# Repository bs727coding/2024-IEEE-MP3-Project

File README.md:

# 2024-IEEE-MP3-Project

A simple media player with bluetooth support using an ESP32, LCD display, audio driver, battery, and button controls.

This is a part of the Brigham Young University IEEE student branch 2024-2025 project.

There are 4 outcomes we hope to accomplish with this project. These are:

    Develop an understanding of KiCAD and PCB design, including footprint design, schematic development, and design rules.
    Learn embedded programming by using FreeRTOS and C to program an ESP32 microcontroller to process media files and control its input and output functions.
    Acquire skill in how to use CAD softwares to design an appropriate chassis for electrical components.
    Become confident and consistent in electrical engineering project documentation.

We anticipate this project will be exciting, challenging, and provide participating students an opportunity to grow their engineering skills outside of a classroom setting.

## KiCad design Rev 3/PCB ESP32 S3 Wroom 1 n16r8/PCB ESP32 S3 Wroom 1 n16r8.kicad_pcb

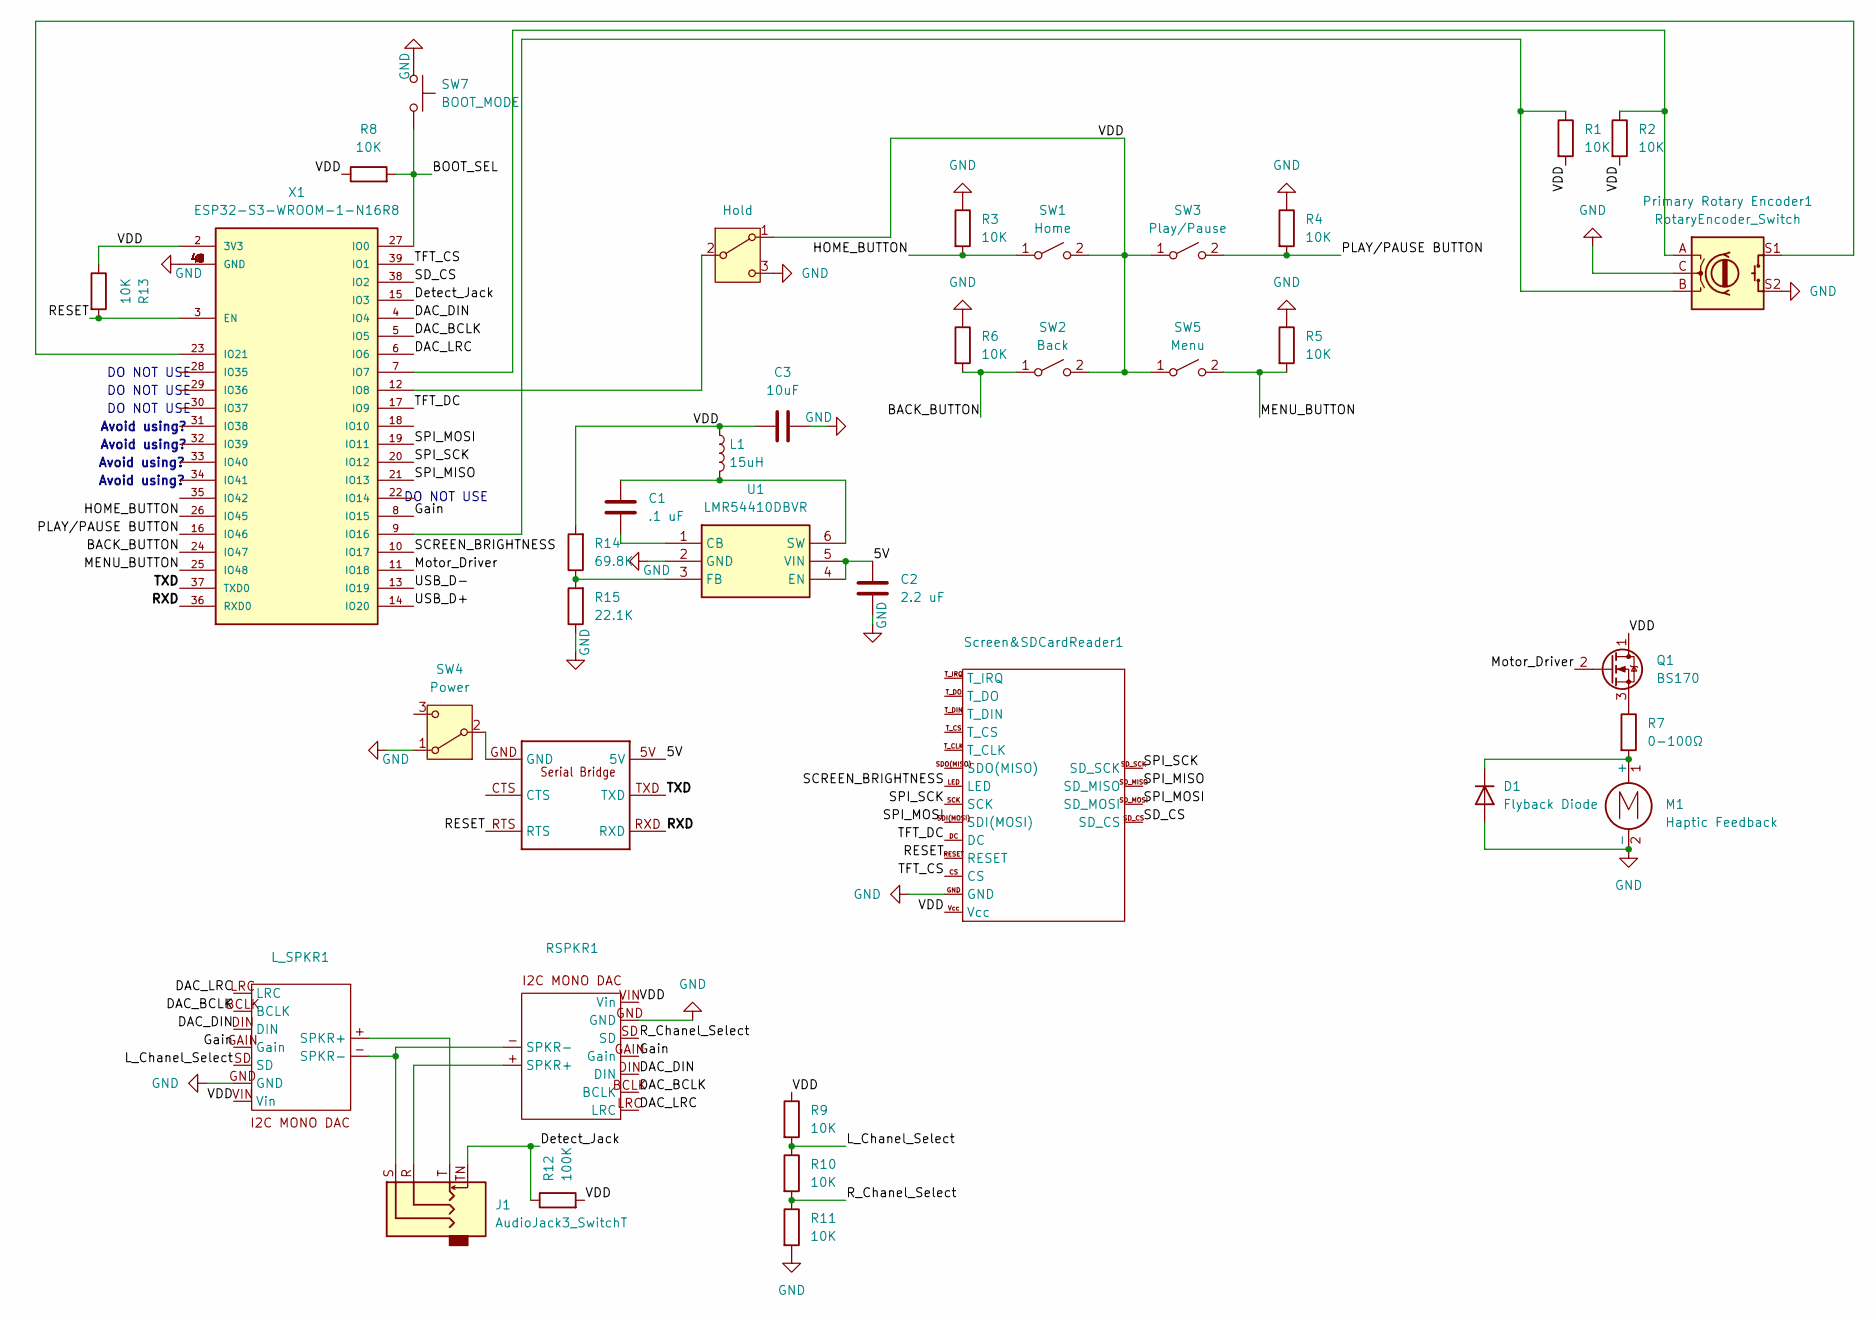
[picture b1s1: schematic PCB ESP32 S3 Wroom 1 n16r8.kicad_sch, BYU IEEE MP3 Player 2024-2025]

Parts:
1: UART_FTDI
C1: .1 uF; C_0603_1608Metric
C2: 2.2 uF; C_0603_1608Metric
C3: 10uF; C_0603_1608Metric
D1: Flyback Diode; D_A-405_P7.62mm_Horizontal
J1: AudioJack3_SwitchT; Jack_3.5mm_CUI_SJ1-3524N_Horizontal
L1: 15uH; L_Vishay_IFSC-1515AH_4x4x1.8mm
L_SPKR1: MAX98357 I2C Audio Driver
M1: Haptic Feedback; TerminalBlock_RND_205-00001_1x02_P5.00mm_Horizontal
Primary Rotary Encoder1: RotaryEncoder_Switch; RotaryEncoder_Alps_EC11E-Switch_Vertical_H20mm
Q1: BS170; TO-92_Inline
R1, R2, R3, R4, R5, R6, R8, R9, R10, R11, R13: 10K; R_Axial_DIN0204_L3.6mm_D1.6mm_P7.62mm_Horizontal
R7: 0-100Ω; R_Axial_DIN0204_L3.6mm_D1.6mm_P7.62mm_Horizontal
R12: 100K; R_Axial_DIN0204_L3.6mm_D1.6mm_P7.62mm_Horizontal
R14: 69.8K; R_01005_0402Metric_Pad0.57x0.30mm_HandSolder
R15: 22.1K; R_01005_0402Metric_Pad0.57x0.30mm_HandSolder
RSPKR1: MAX98357 I2C Audio Driver
SW1: Home; Kailh_socket_PG1350
SW2: Back; Kailh_socket_PG1350
SW3: Play/Pause; Kailh_socket_PG1350
SW4: Power; SW_Slide_SPDT_Angled_CK_OS102011MA1Q
SW5: Menu; Kailh_socket_PG1350
SW6: Hold; SW_Slide_SPDT_Angled_CK_OS102011MA1Q
SW7: BOOT_MODE; SW_PUSH_6mm
Screen&SDCardReader1: 2.4'_TFT_SPI_ILI9341_WITH_SD_CARD
U1: LMR54410DBVR; SOT95P280X145-6N; Mouser Part Number 595-LMR54410DBVR
X1: ESP32-S3-WROOM-1-N16R8; ESP32S3WROOM1N8R2; MANUFACTURER_PART_NUMBER ESP32-S3-WROOM-1-N16R8

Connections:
/5V: 1.5V, C2.2, U1.4 (EN), U1.5 (VIN)
/BACK_BUTTON: R6.2, SW2.1 (A), X1.24 (IO47)
/BOOT_SEL: R8.2, SW7.2, X1.27 (IO0)
/DAC_BCLK: L_SPKR1.BCLK, RSPKR1.BCLK, X1.5 (IO5)
/DAC_DIN: L_SPKR1.DIN, RSPKR1.DIN, X1.4 (IO4)
/DAC_LRC: L_SPKR1.LRC, RSPKR1.LRC, X1.6 (IO6)
/Detect_Jack: J1.TN, R12.1, X1.15 (IO3)
/Gain: L_SPKR1.GAIN (Gain), RSPKR1.GAIN (Gain), X1.8 (IO15)
/HOME_BUTTON: R3.2, SW1.1 (A), X1.26 (IO45)
/L_Chanel_Select: L_SPKR1.SD, R9.2, R10.1
/MENU_BUTTON: R5.2, SW5.2 (B), X1.25 (IO48)
/Motor_Driver: Q1.2 (G), X1.11 (IO18)
/PLAY/PAUSE BUTTON: R4.2, SW3.2 (B), X1.16 (IO46)
/RESET: 1.RTS, R13.2, Screen&SDCardReader1.RESET, X1.3 (EN)
/RXD: 1.RXD, X1.36 (RXD0)
/R_Chanel_Select: R10.2, R11.1, RSPKR1.SD
/SCREEN_BRIGHTNESS: Screen&SDCardReader1.LED, X1.10 (IO17)
/SD_CS: Screen&SDCardReader1.SD_CS, X1.38 (IO2)
/SPI_MISO: Screen&SDCardReader1.SD_MISO, X1.21 (IO13)
/SPI_MOSI: Screen&SDCardReader1.SDI(MOSI), Screen&SDCardReader1.SD_MOSI, X1.19 (IO11)
/SPI_SCK: Screen&SDCardReader1.SCK, Screen&SDCardReader1.SD_SCK, X1.20 (IO12)
/TFT_CS: Screen&SDCardReader1.CS, X1.39 (IO1)
/TFT_DC: Screen&SDCardReader1.DC, X1.17 (IO9)
/TXD: 1.TXD, X1.37 (TXD0)
/USB_D+: X1.14 (IO20)
/USB_D-: X1.13 (IO19)
/VDD: C3.2, L1.1, L_SPKR1.VIN (Vin), Q1.1 (D), R1.2, R2.2, R8.1, R9.1, R12.2, R13.1, R14.2, RSPKR1.VIN (Vin), SW1.2 (B), SW2.2 (B), SW3.1 (A), SW5.1 (A), SW6.1 (A), Screen&SDCardReader1.Vcc, X1.2 (3V3)
GND: C2.1, C3.1, D1.2 (A), L_SPKR1.GND, M1.2 (-), Primary Rotary Encoder1.C, Primary Rotary Encoder1.S2, R3.1, R4.1, R5.1, R6.1, R11.2, R15.1, RSPKR1.GND, SW4.1 (A), SW6.3 (C), SW7.1, Screen&SDCardReader1.GND, U1.2 (GND), X1.1 (GND), X1.40 (GND), X1.41 (GND), X1.42 (GND), X1.43 (GND), X1.44 (GND), X1.45 (GND), X1.46 (GND), X1.47 (GND), X1.48 (GND), X1.49 (GND)
unnamed: D1.1 (K), M1.1 (+), R7.2
unnamed: J1.T, L_SPKR1.+ (SPKR+)
unnamed: J1.S, L_SPKR1.- (SPKR-), RSPKR1.- (SPKR-)
unnamed: Q1.3 (S), R7.1
unnamed: J1.R, RSPKR1.+ (SPKR+)
unnamed: 1.GND, SW4.2 (B)
unnamed: SW6.2 (B), X1.12 (IO8)
unnamed: C1.2, U1.1 (CB)
unnamed: R14.1, R15.2, U1.3 (FB)
unnamed: C1.1, L1.2, U1.6 (SW)
unnamed: Primary Rotary Encoder1.A, R2.1, X1.7 (IO7)
unnamed: Primary Rotary Encoder1.B, R1.1, X1.9 (IO16)
unnamed: Primary Rotary Encoder1.S1, X1.23 (IO21)

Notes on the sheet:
Avoid using?
DO NOT USE

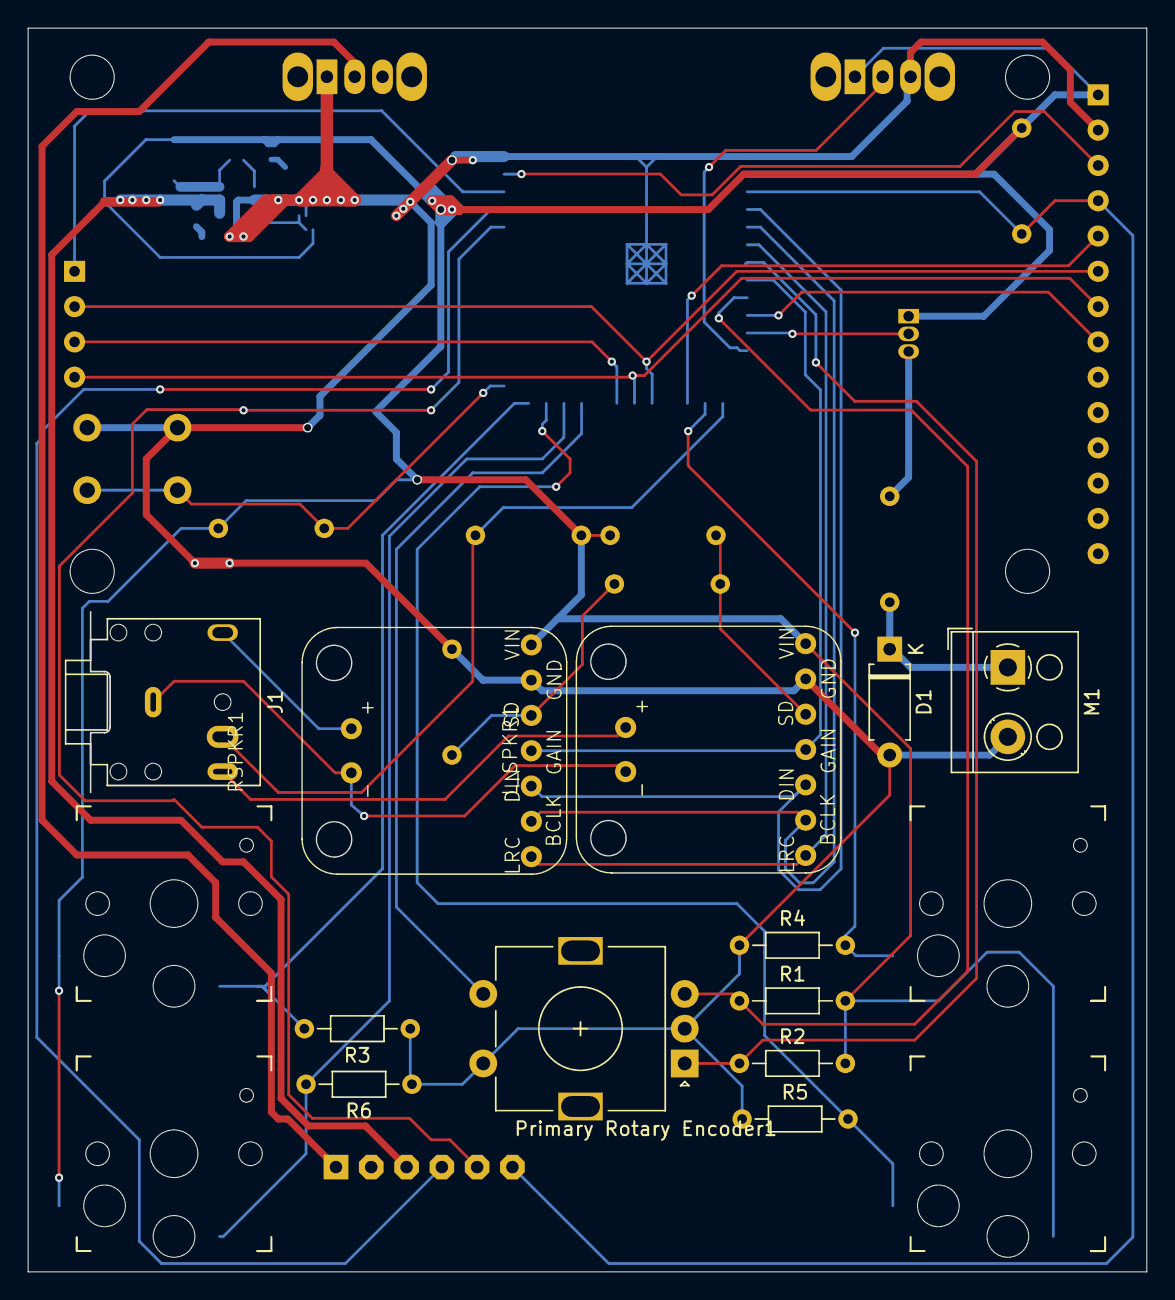
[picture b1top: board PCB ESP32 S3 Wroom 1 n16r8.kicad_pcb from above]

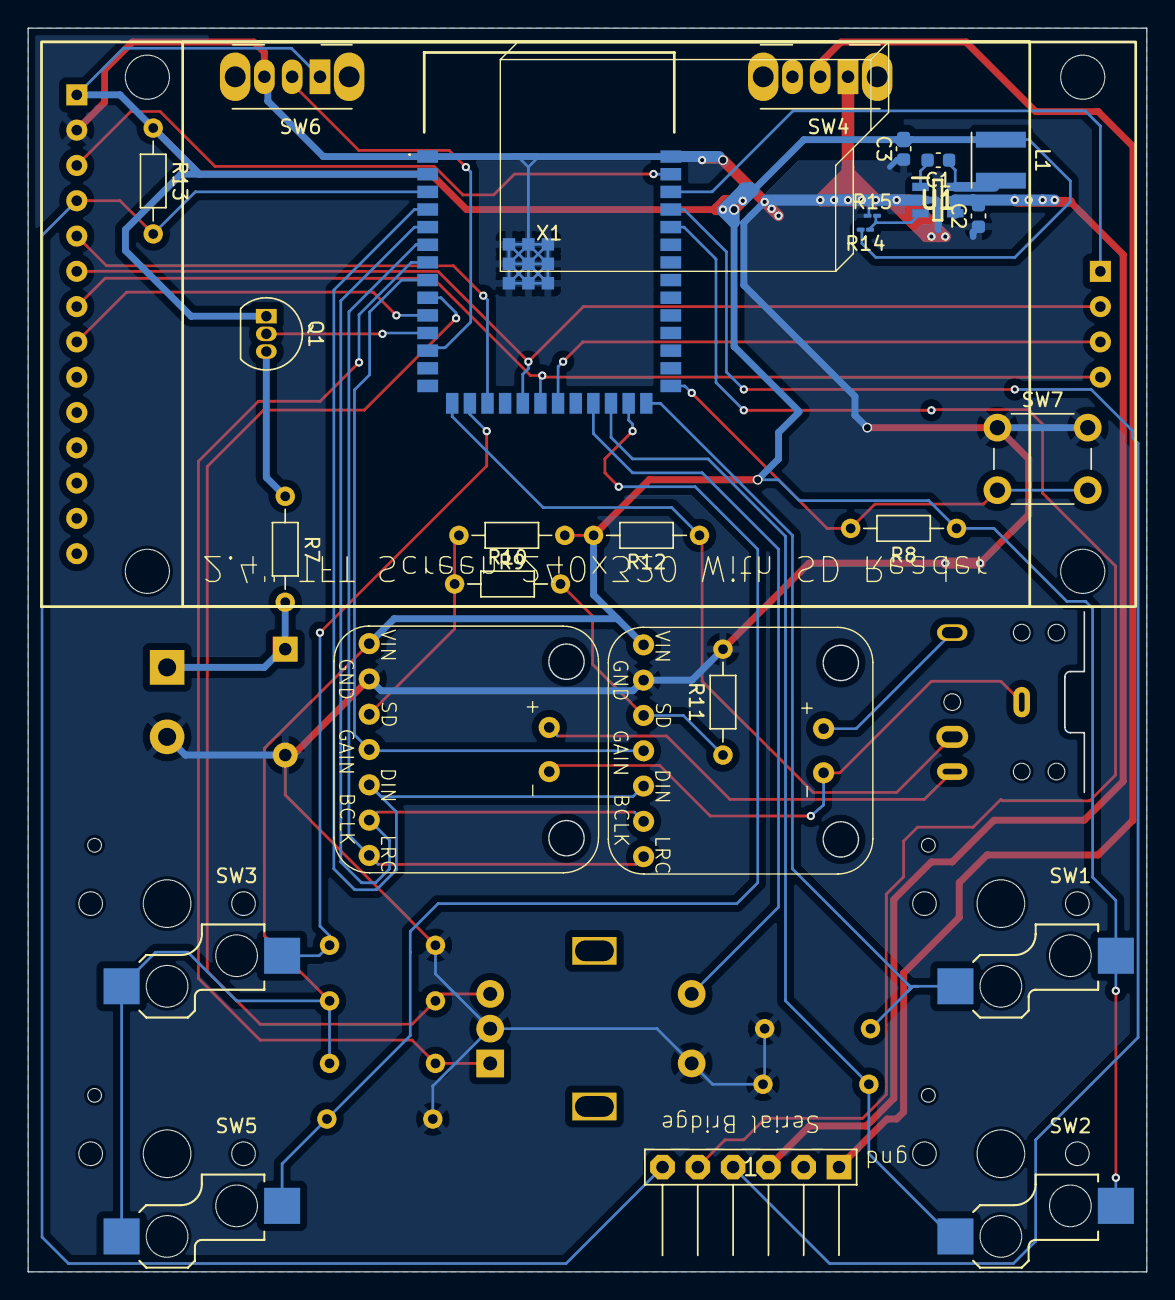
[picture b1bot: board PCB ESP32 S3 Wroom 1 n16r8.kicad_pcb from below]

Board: 2 copper layers, 80.5 x 89.5 mm, 37 parts (20 on the bottom side), 39 nets.

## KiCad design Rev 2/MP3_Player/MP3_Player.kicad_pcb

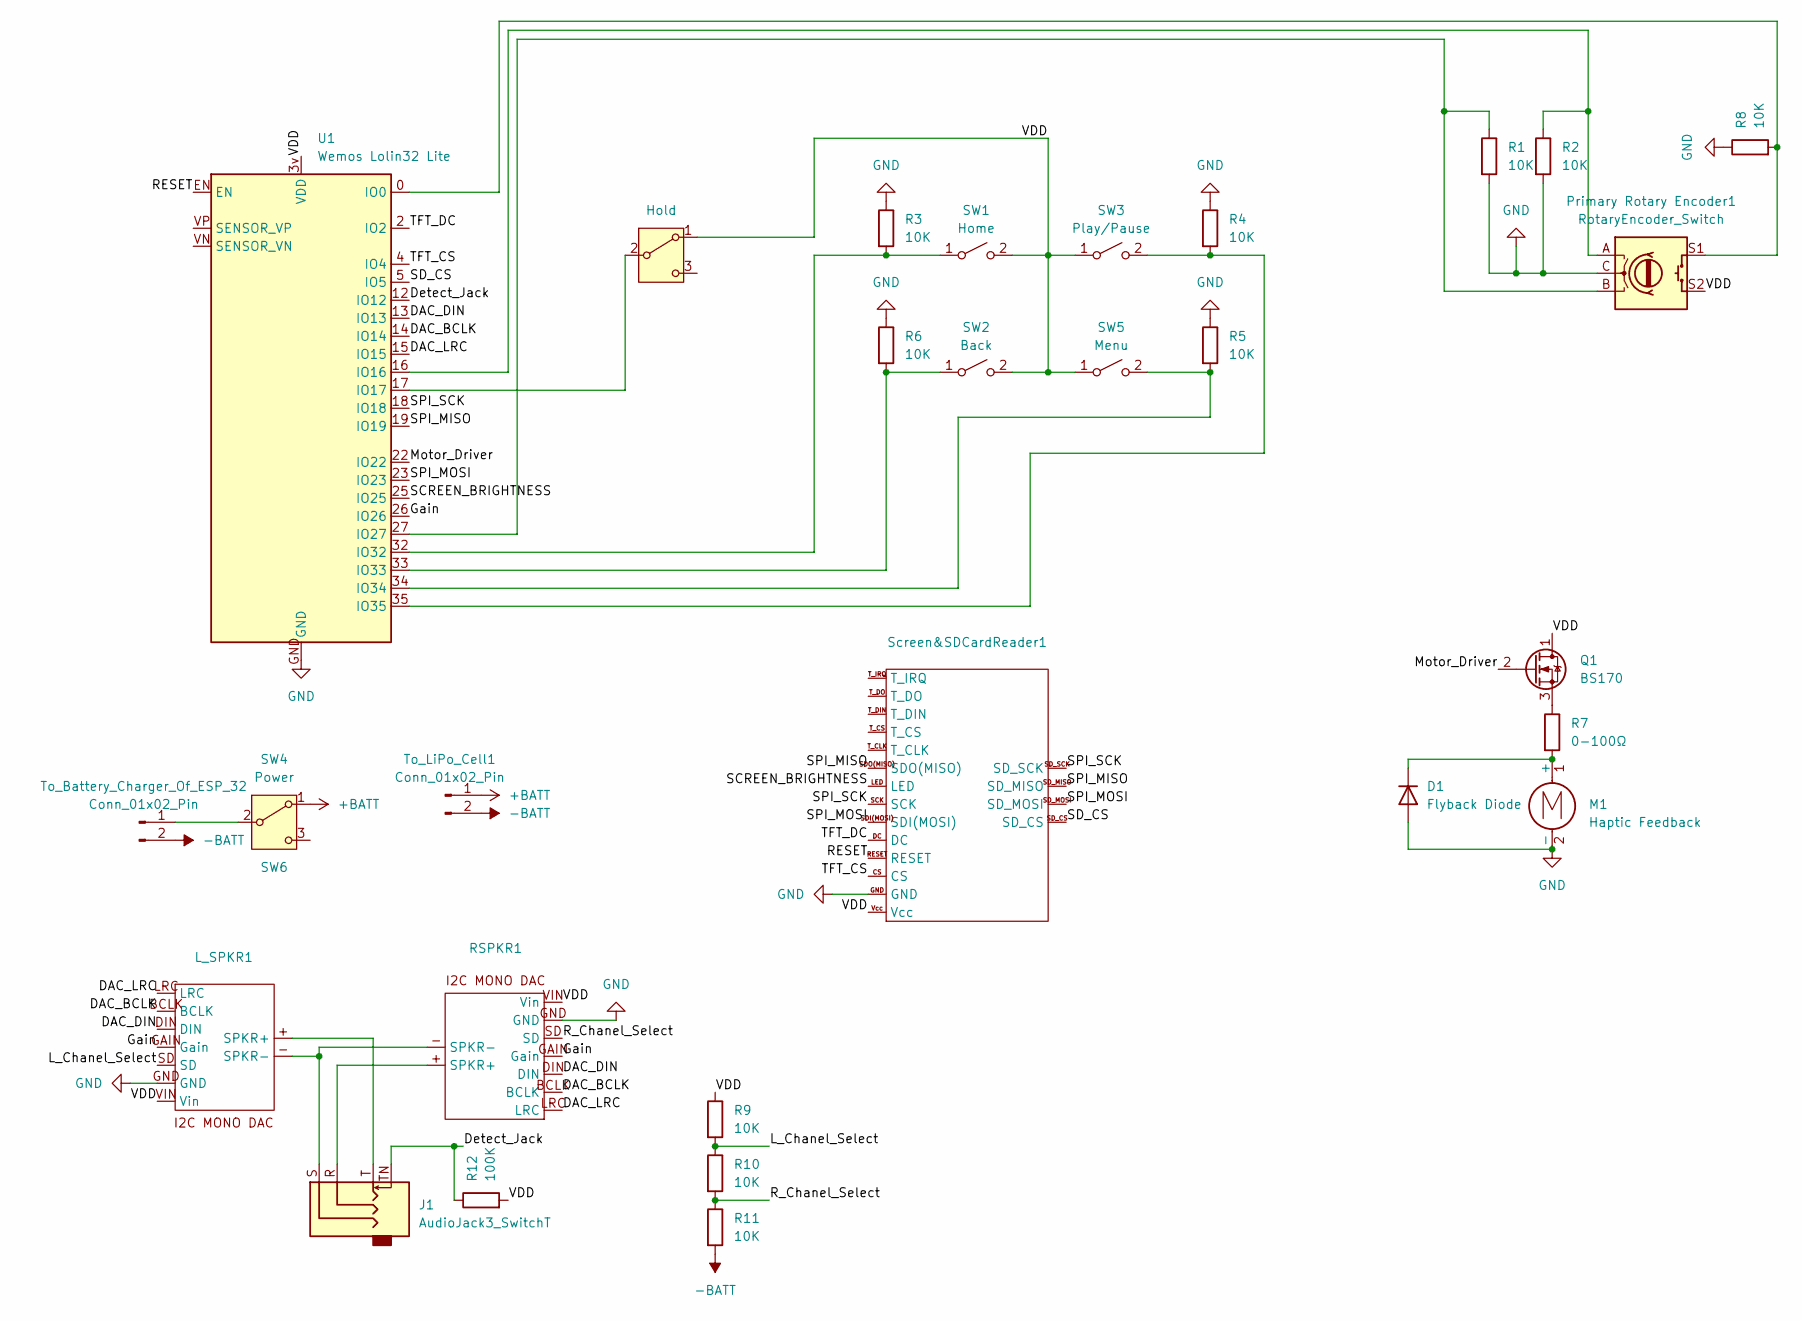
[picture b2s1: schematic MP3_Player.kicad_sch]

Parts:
D1: Flyback Diode; D_A-405_P7.62mm_Horizontal
J1: AudioJack3_SwitchT; Jack_3.5mm_CUI_SJ1-3524N_Horizontal
L_SPKR1: MAX98357 I2C Audio Driver
M1: Haptic Feedback; TerminalBlock_RND_205-00001_1x02_P5.00mm_Horizontal
Primary Rotary Encoder1: RotaryEncoder_Switch; RotaryEncoder_Alps_EC11E-Switch_Vertical_H20mm
Q1: BS170; TO-92_Inline
R1, R2, R3, R4, R5, R6, R8, R9, R10, R11: 10K; R_Axial_DIN0204_L3.6mm_D1.6mm_P7.62mm_Horizontal
R7: 0-100Ω; R_Axial_DIN0204_L3.6mm_D1.6mm_P7.62mm_Horizontal
R12: 100K; R_Axial_DIN0204_L3.6mm_D1.6mm_P7.62mm_Horizontal
RSPKR1: MAX98357 I2C Audio Driver
SW1: Home; Kailh_socket_PG1350
SW2: Back; Kailh_socket_PG1350
SW3: Play/Pause; Kailh_socket_PG1350
SW4: Power; SW_Slide_SPDT_Angled_CK_OS102011MA1Q
SW5: Menu; Kailh_socket_PG1350
SW6: Hold; SW_Slide_SPDT_Angled_CK_OS102011MA1Q
Screen&SDCardReader1: 2.4'_TFT_SPI_ILI9341_WITH_SD_CARD
To_Battery_Charger_Of_ESP_32: Conn_01x02_Pin; JST_XA_B02B-XASK-1-A_1x02_P2.50mm_Vertical
To_LiPo_Cell1: Conn_01x02_Pin; JST_XA_B02B-XASK-1-A_1x02_P2.50mm_Vertical
U1: Wemos Lolin32 Lite; Wemos Lolin32 Lite v1.0.0

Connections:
+BATT: SW4.1 (A), To_LiPo_Cell1.1
-BATT: R11.2, To_Battery_Charger_Of_ESP_32.2, To_LiPo_Cell1.2
/DAC_BCLK: L_SPKR1.BCLK, RSPKR1.BCLK, U1.14 (IO14)
/DAC_DIN: L_SPKR1.DIN, RSPKR1.DIN, U1.13 (IO13)
/DAC_LRC: L_SPKR1.LRC, RSPKR1.LRC, U1.15 (IO15)
/Detect_Jack: J1.TN, R12.1, U1.12 (IO12)
/Gain: L_SPKR1.GAIN (Gain), RSPKR1.GAIN (Gain), U1.26 (IO26)
/L_Chanel_Select: L_SPKR1.SD, R9.2, R10.1
/Motor_Driver: Q1.2 (G), U1.22 (IO22)
/RESET: Screen&SDCardReader1.RESET, U1.EN
/R_Chanel_Select: R10.2, R11.1, RSPKR1.SD
/SCREEN_BRIGHTNESS: Screen&SDCardReader1.LED, U1.25 (IO25)
/SD_CS: Screen&SDCardReader1.SD_CS, U1.5 (IO5)
/SPI_MISO: Screen&SDCardReader1.SDO(MISO), Screen&SDCardReader1.SD_MISO, U1.19 (IO19)
/SPI_MOSI: Screen&SDCardReader1.SDI(MOSI), Screen&SDCardReader1.SD_MOSI, U1.23 (IO23)
/SPI_SCK: Screen&SDCardReader1.SCK, Screen&SDCardReader1.SD_SCK, U1.18 (IO18)
/TFT_CS: Screen&SDCardReader1.CS, U1.4 (IO4)
/TFT_DC: Screen&SDCardReader1.DC, U1.2 (IO2)
/VDD: L_SPKR1.VIN (Vin), Primary Rotary Encoder1.S2, Q1.1 (D), R9.1, R12.2, RSPKR1.VIN (Vin), SW1.2 (B), SW2.2 (B), SW3.1 (A), SW5.1 (A), SW6.1 (A), Screen&SDCardReader1.Vcc, U1.3v (VDD)
GND: D1.2 (A), L_SPKR1.GND, M1.2 (-), Primary Rotary Encoder1.C, R1.2, R2.2, R3.1, R4.1, R5.1, R6.1, R8.1, RSPKR1.GND, Screen&SDCardReader1.GND, U1.GND
unnamed: D1.1 (K), M1.1 (+), R7.2
unnamed: J1.T, L_SPKR1.+ (SPKR+)
unnamed: J1.S, L_SPKR1.- (SPKR-), RSPKR1.- (SPKR-)
unnamed: Q1.3 (S), R7.1
unnamed: J1.R, RSPKR1.+ (SPKR+)
unnamed: R3.2, SW1.1 (A), U1.32 (IO32)
unnamed: R6.2, SW2.1 (A), U1.33 (IO33)
unnamed: R4.2, SW3.2 (B), U1.35 (IO35)
unnamed: SW4.2 (B), To_Battery_Charger_Of_ESP_32.1
unnamed: R5.2, SW5.2 (B), U1.34 (IO34)
unnamed: SW6.2 (B), U1.17 (IO17)
unnamed: Primary Rotary Encoder1.S1, R8.2, U1.0 (IO0)
unnamed: Primary Rotary Encoder1.A, R2.1, U1.16 (IO16)
unnamed: Primary Rotary Encoder1.B, R1.1, U1.27 (IO27)

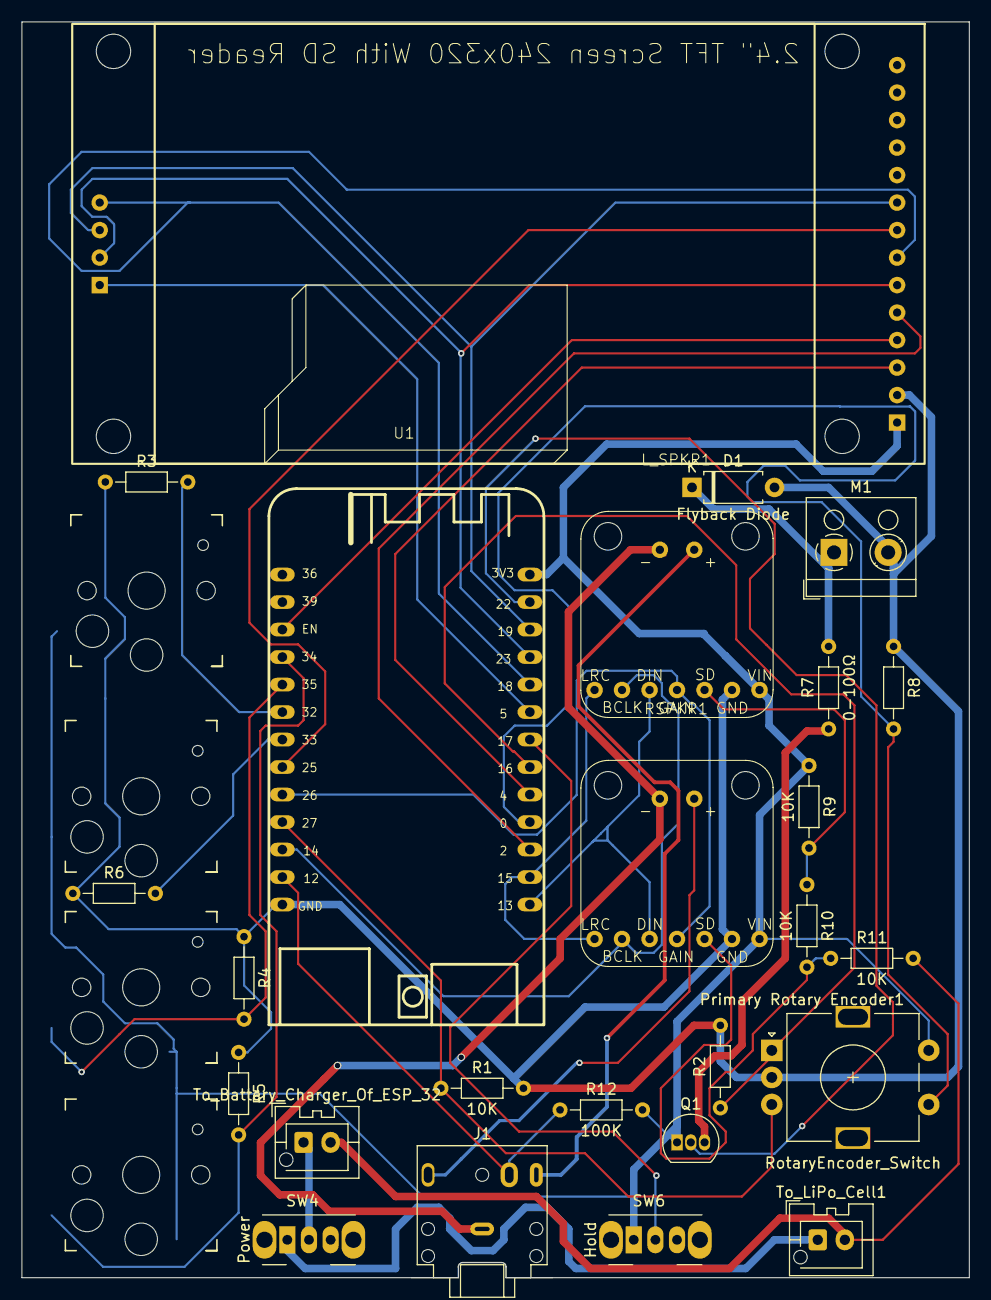
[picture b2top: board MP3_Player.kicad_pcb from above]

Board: 2 copper layers, 87.5 x 116.0 mm, 29 parts (1 on the bottom side), 34 nets.

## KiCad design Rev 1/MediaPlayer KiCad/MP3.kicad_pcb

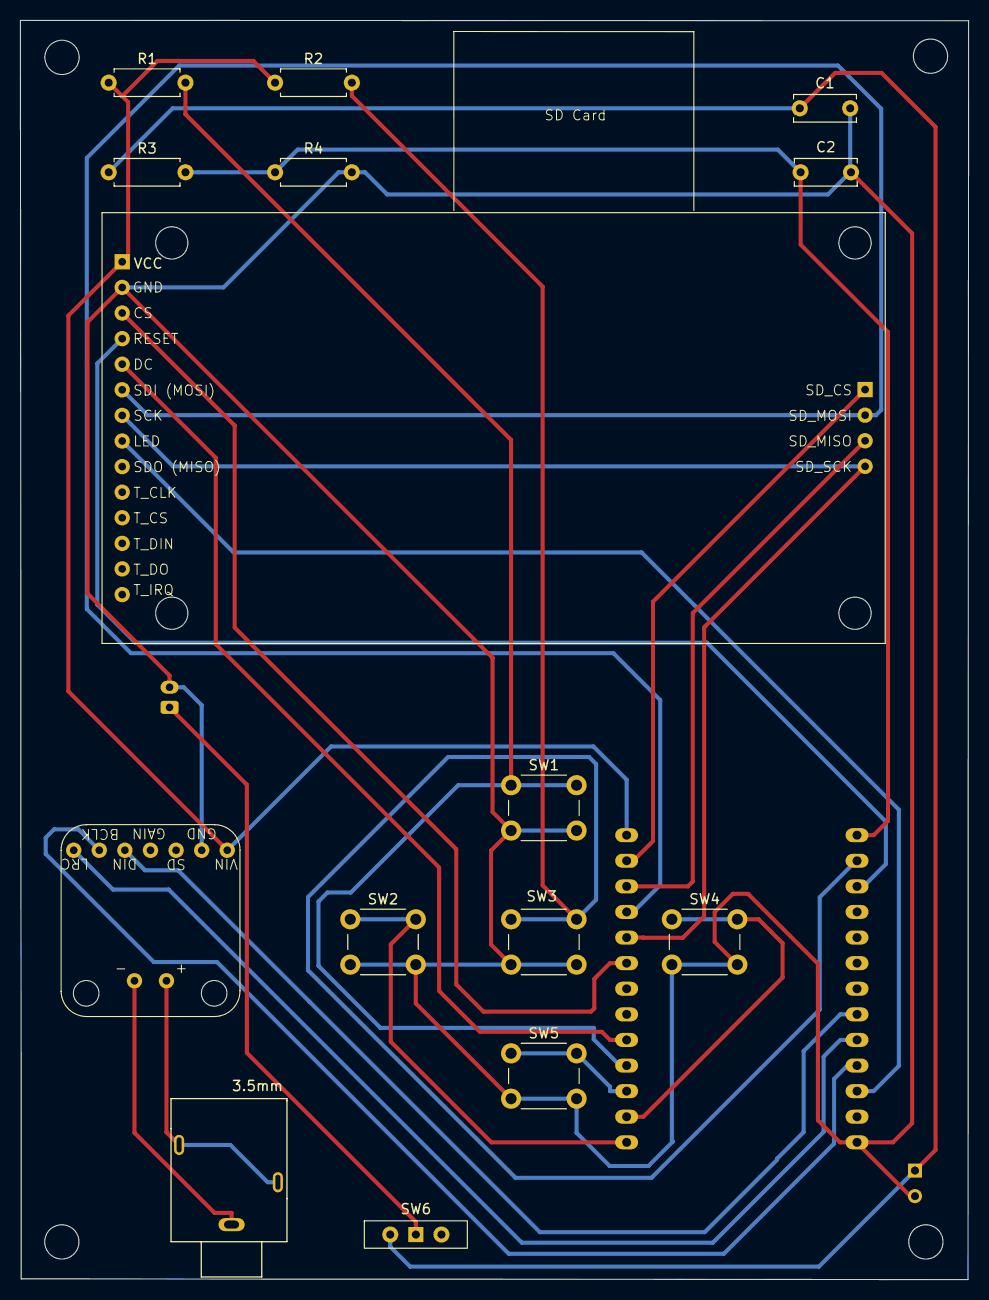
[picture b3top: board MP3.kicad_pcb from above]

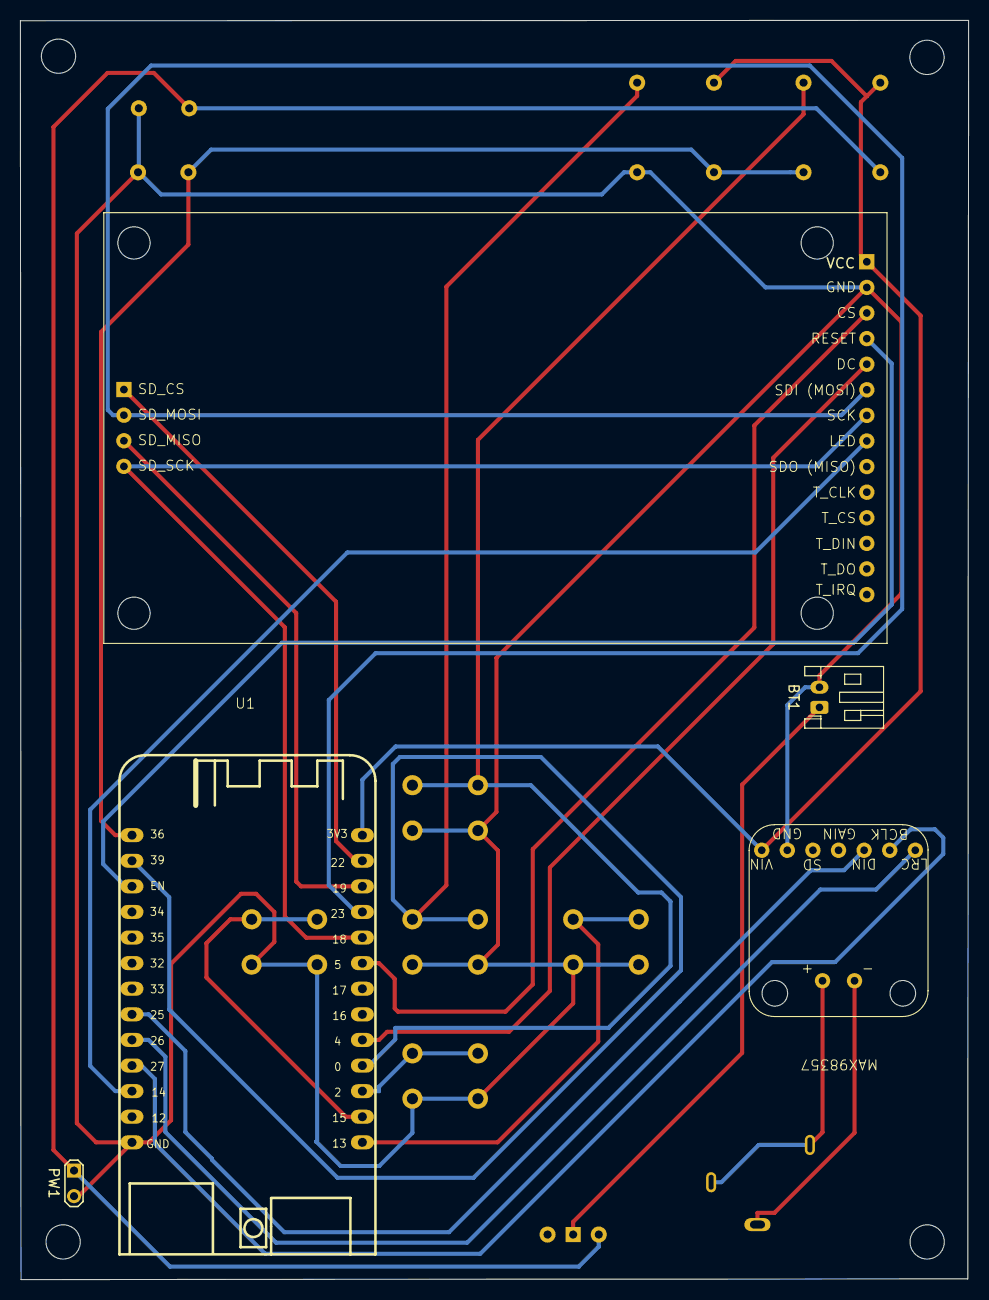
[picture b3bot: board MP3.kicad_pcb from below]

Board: 2 copper layers, 94.1 x 125.0 mm, 17 parts (4 on the bottom side), 15 nets.

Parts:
3.5mm: WENZHOU_PJ324M_2
BT1: JST_PH_S2B-PH-K_1x02_P2.00mm_Horizontal
C1: C1; C_Disc_D6.0mm_W2.5mm_P5.00mm
C2: C2; C_Disc_D6.0mm_W2.5mm_P5.00mm
MAX98357: MAX98357 I2C Audio Driver
PW1: TestPoint_2Pads_Pitch2.54mm_Drill0.8mm
R1: R1; R_Axial_DIN0207_L6.3mm_D2.5mm_P7.62mm_Horizontal
R2: R2; R_Axial_DIN0207_L6.3mm_D2.5mm_P7.62mm_Horizontal
R3: R3; R_Axial_DIN0207_L6.3mm_D2.5mm_P7.62mm_Horizontal
R4: R4; R_Axial_DIN0207_L6.3mm_D2.5mm_P7.62mm_Horizontal
SW1, SW2, SW3, SW4, SW5: SW_PUSH_6mm
SW6: SW_Slide-03_Wuerth-WS-SLTV_10x2.5x6.4_P2.54mm
U1: Wemos Lolin32 Lite v1.0.0

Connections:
GND: BT1.2, C1.2, C2.2, MAX98357.GND, PW1.1, R4.2, SW1.2, SW2.2, SW3.2, SW4.2, SW5.2, U1.GND
MAX_BCLK: MAX98357.BCLK, U1.27
MAX_DIN: MAX98357.DIN, U1.25
MAX_LRC: MAX98357.LRC, U1.26
PWR: BT1.1, SW6.1
SW1: R1.2, SW1.1, U1.0
SW2: SW2.1, U1.13
SW3: R2.2, SW3.1, U1.VN
SW4: SW4.1, U1.15
SW5: SW5.1, U1.2
VCC: MAX98357.VIN, R1.1, R2.1, U1.3v
VCC2: C1.1, PW1.2, R3.1, SW6.2
VP: C2.1, R3.2, R4.1, U1.VP
audio+: 3.5mm.2 (R), 3.5mm.5 (L), MAX98357.+
audio-: 3.5mm.1 (GND), MAX98357.-

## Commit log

2024-10-17 Added KiCad project files and readme.md file
2024-10-17 Added plans for 1st rev
2024-10-24 Test, moved around files
2024-10-24 Rev 2 upload
2024-10-24 added esp32
2024-10-24 added some parts
2024-10-24 Finished Setup
2024-10-26 W/ Wired Rotary Encoder
2024-10-28 fixed some save bugs
2024-10-29 W/ Wired Rotary Encoder Switches & Keys
2024-10-29 Added pullup on the buttons
    And also a pulldown resistor on the rotary encoder
2024-10-30 Finished Wiring
    Edits:
    -Added I2S interface for headphones.
    *Chanel select is dependent on voltage on pin SD
    *Gain is hooked up to ESP32 onboard DAC
    *Detect Pin is added to know if headphones are plugged in/unplugged
    -Moved Pins around for our specific pinout.
2024-10-30 Fixed pinout
    -Edited ESP32 pinout so that it links correctly with the provided footprint
    -Re-routed some affected pins
    -Added correct pinout image
2024-10-30 Fixed Power Switch
    -Fixed Wiring so power switch is interrupting the battery on its way to the battery charger
    -Fixed Footprint linking issues
2024-10-30 added functionality to game creation and fetching
2024-10-31 Layed out PCB
2024-10-31 wired power and ground
2024-10-31 Fixed Track width of ground to screen
2024-10-31 Imported ECE Shop DRC
    -Imported DRC so we have the option open to print at the shop
    -Fixed one trace that was close to a drill hole
2024-11-01 Added Flyback Diode
    -Added Flyback Diode to prevent sparking and unwanted behavior
    -Finished high power rails
    -Fixed Screen Orientation
    -Fixed Placement of some components
    -Fixed Silkscreen
2024-11-02 Almost finished routing traces
2024-11-03 Forgot to add new backup files
2024-11-07 Finished routing PCB
2024-11-07 created fabrication files
2024-11-08 changed the name to version 1
2024-11-21 uploaded final version
2025-02-07 began work on rev 3
2025-02-07 updated margins on esp32
    - to prevent traces under antenna
2025-02-07 wired up ESP32 to the best of my knowledge
2025-02-07 reverted pins for USB
2025-02-07 added datasheet
2025-02-07 updated schematic using datasheet
    - checked documentation on all pins
    - added FTDI header, minus 5V to 3v3 Regulator
2025-02-07 Renamed Sheet
2025-02-07 added Kailh switch 3d model for renders
2025-02-08 Added More 3d Models
2025-02-11 added 3v3 regulator
2025-02-11 Routed more vias
2025-02-11 finished traces
2025-02-11 updated d2 footprint
    -1A, 40 V Schottky rectifier per datasheet
    -package size determined from digikey
2025-02-11 updated inductor footprint
    to be a standard 2424 (6060 metric) mount for a power rectifier.
2025-02-18 changed out power regulator
    - JLCPCB part package sizes
    - new chip supports 4.5v-36v so it will work with usb power
2025-02-18 closed the program
    so that others don't get a warning
2025-02-20 updated mfg files
2025-02-20 updated power regulator circuit
2025-02-20 fixed a trace
2025-02-21 added esp to BOM
2025-03-06 updated pcb and fixed footprints
2025-04-03 changed FileHandler to be OOP
